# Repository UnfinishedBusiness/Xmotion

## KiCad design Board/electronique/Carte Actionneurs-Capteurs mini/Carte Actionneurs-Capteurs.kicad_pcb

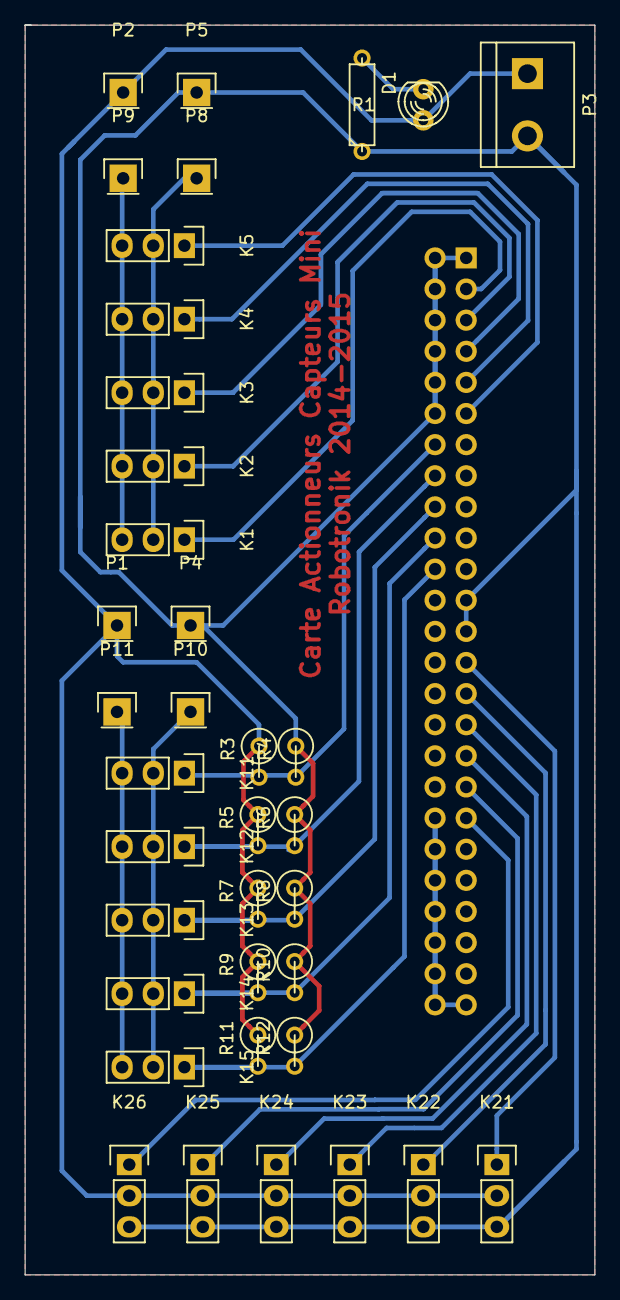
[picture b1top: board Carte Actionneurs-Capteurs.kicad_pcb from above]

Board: 2 copper layers, 46.5 x 102.0 mm, 38 parts (1 on the bottom side), 23 nets.

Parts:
D1: LED; LED-3MM
K1, K2, K3, K4, K5, K11, K12, K13, K14, K15, K21, K22, K23, K24, K25, K26: CONN_01X03; Pin_Header_Straight_1x03
P1, P2, P4, P5, P8, P9, P10, P11: CONN_1; Pin_Header_Straight_1x01
P3: CONN_2; bornier2
P6: CONN_25X2; Pin_Header_Straight_2x25
R1: R; R3
R3, R4, R5, R6, R7, R8, R9, R10, R11, R12: R; R1

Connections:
ADC1: K1.1, P6.3
ADC2: K2.1, P6.5
ADC3: K3.1, P6.7
ADC4: K4.1, P6.9
ADC5: K5.1, P6.11
IO1: K11.1, P6.14, R3.2, R4.2
IO2: K12.1, P6.16, R5.2, R6.2
IO3: K13.1, P6.18, R7.2, R8.2
IO4: K14.1, P6.20, R9.2, R10.2
IO5: K15.1, P6.22, R11.2, R12.2
unnamed: D1.2, R1.2
PWM1: K21.1, P6.27
PWM2: K22.1, P6.29
PWM3: K23.1, P6.31
PWM4: K24.1, P6.33
PWM5: K25.1, P6.35
PWM6: K26.1, P6.37
PWR_ADC_1: K1.2, K2.2, K3.2, K4.2, K5.2, P8.1
PWR_ADC_2: K1.3, K2.3, K3.3, K4.3, K5.3, P9.1
PWR_ADC_3: D1.1, K21.2, K22.2, K23.2, K24.2, K25.2, K26.2, P1.1, P2.1, P3.1, R3.1, R5.1, R7.1, R9.1, R11.1
PWR_ADC_4: K21.3, K22.3, K23.3, K24.3, K25.3, K26.3, P3.2, P4.1, P5.1, P6.1, P6.2, P6.4, P6.6, P6.8, P6.10, P6.12, P6.23, P6.25, P6.38, P6.40, P6.42, P6.44, P6.46, P6.48, P6.49, P6.50, R1.1, R4.1, R6.1, R8.1, R10.1, R12.1
PWR_IO_1: K11.2, K12.2, K13.2, K14.2, K15.2, P10.1
PWR_IO_2: K11.3, K12.3, K13.3, K14.3, K15.3, P11.1

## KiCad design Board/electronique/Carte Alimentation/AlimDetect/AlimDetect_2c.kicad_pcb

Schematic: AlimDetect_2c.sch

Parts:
C1: 0.33µ; C_0603_HandSoldering
C3: 0.1µ; C_0603_HandSoldering
C4: C; C_Radial_D18_L36_P7.5
D1, D6: LED; LED-3MM
D2: 1N5404; Diode_DO-201AD_Horizontal_RM15
D3, D4: LED; LED_0603
D5: ZENER; D3
F1: FUSE; Fuseholder5x20_horiz_open_inline_Type-I
K1: CONN_01X03; Pin_Header_Angled_1x03
P1, P2, P3: CONN_01X02; bornier2
P4: CONN_01X02; Pin_Header_Straight_1x02
R1, R2, R3, R5, R6, R7, R8, R9: R; R_0603_HandSoldering
R4: 820; Resistor_Horizontal_RM10mm
R10, R11: 15k; R_0603_HandSoldering
R12, R13: 150; R_0603_HandSoldering
R14: 82; R_0603_HandSoldering
R15: 380; Resistor_Horizontal_RM10mm
R16, R17: 250; R_0603_HandSoldering
U1: TLC274; SOIC-14_3.9x8.7mm_Pitch1.27mm
U3: 74LS08; SOIC-14_3.9x8.7mm_Pitch1.27mm
U4: KMIG1240; kmig1240
U5: 7805; TO-220_Neutral123_Horizontal

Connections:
+5V: C3.1, P2.2, R14.1, U3.14, U4.1, U5.3 (VO)
/Vref: D5.1, R14.2, U1.9, U1.13
/elec_redressé: C1.1, C4.1, D2.1, P3.2, U1.4, U5.1 (VI)
GND: C1.2, C3.2, C4.2, D1.1, D3.1, D4.1, D5.2, D6.2, K1.1, P1.1, P2.1, P3.1, R3.2, R6.1, R8.2, R10.2, R11.2, U1.11, U3.1, U3.2, U3.4, U3.5, U3.7, U3.9, U3.10, U5.2 (GND)
unnamed: D1.2, R4.2
unnamed: D2.2, F1.2, R4.1
unnamed: D3.2, R12.2
unnamed: D4.2, R13.2
unnamed: D6.1, R15.2
unnamed: F1.1, P1.2
unnamed: K1.2, R1.1, R7.1
unnamed: K1.3, R2.1, R15.1
unnamed: P4.1, U4.2
unnamed: P4.2, U3.11
unnamed: R1.2, R5.1, U1.2
unnamed: R2.2, R3.1, U1.3
unnamed: R6.2, R9.1, U1.6
unnamed: R7.2, R8.1, U1.5
unnamed: R10.1, R12.1, U1.14, U3.12
unnamed: R11.1, R13.1, U1.8, U3.13
unnamed: R5.2, R16.1, U1.1
unnamed: R16.2, U1.10
unnamed: R9.2, R17.1, U1.7
unnamed: R17.2, U1.12

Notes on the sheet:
IN_DETECT
IN_ELEC
ELEC_REGUL_5V

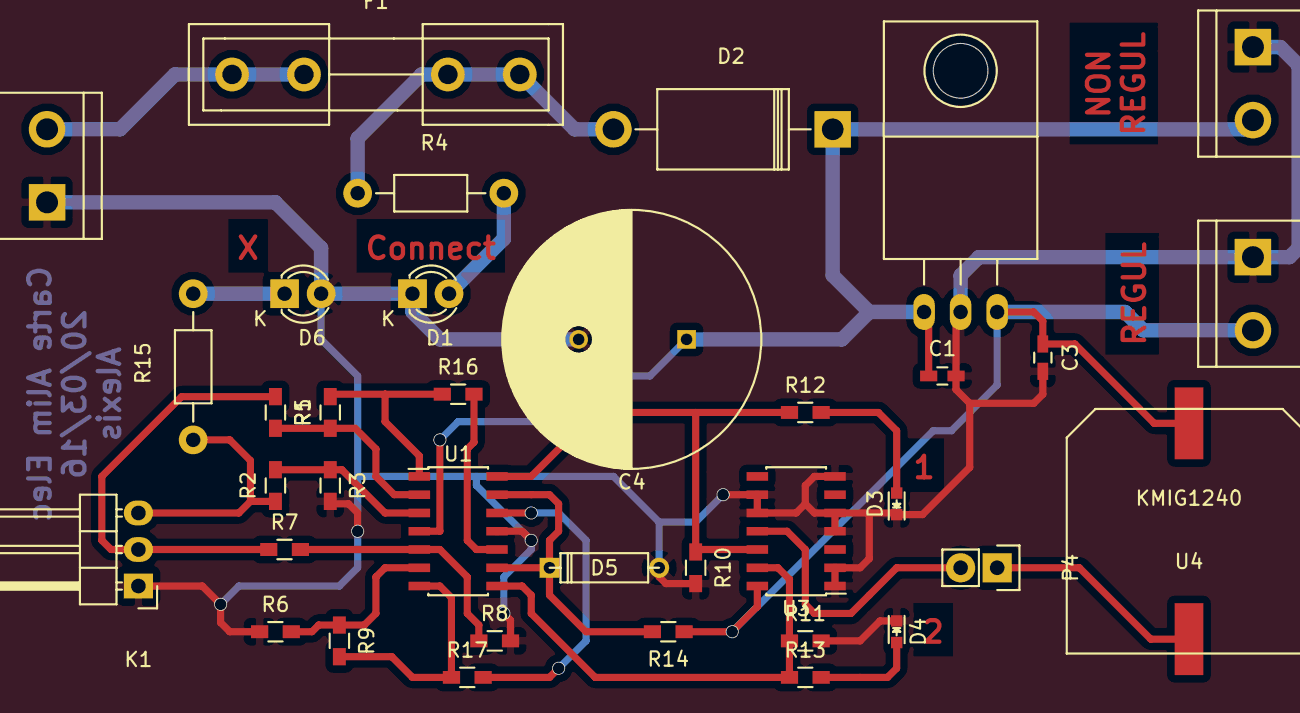
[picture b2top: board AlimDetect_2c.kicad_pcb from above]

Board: 2 copper layers, 36 parts (0 on the bottom side), 24 nets.

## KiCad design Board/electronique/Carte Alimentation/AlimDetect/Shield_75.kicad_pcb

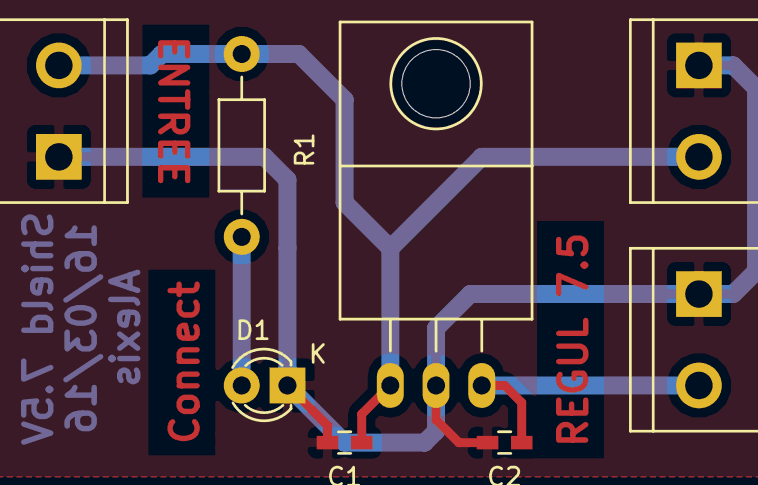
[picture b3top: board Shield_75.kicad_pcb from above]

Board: 2 copper layers, 8 parts (0 on the bottom side), 4 nets.

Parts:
C1, C2: C; C_0603_HandSoldering
D1: LED; LED-3MM
P1, P2, P3: CONN_01X02; bornier2
R1: R; Resistor_Horizontal_RM10mm
U1: 78S75C_correctPin; TO-220_Neutral123_Horizontal

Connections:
GND: C1.2, C2.2, D1.1, P1.1, P2.1, P3.1, U1.2
unnamed: C1.1, P1.2, P3.2, R1.1, U1.1
unnamed: C2.1, P2.2, U1.3
unnamed: D1.2, R1.2

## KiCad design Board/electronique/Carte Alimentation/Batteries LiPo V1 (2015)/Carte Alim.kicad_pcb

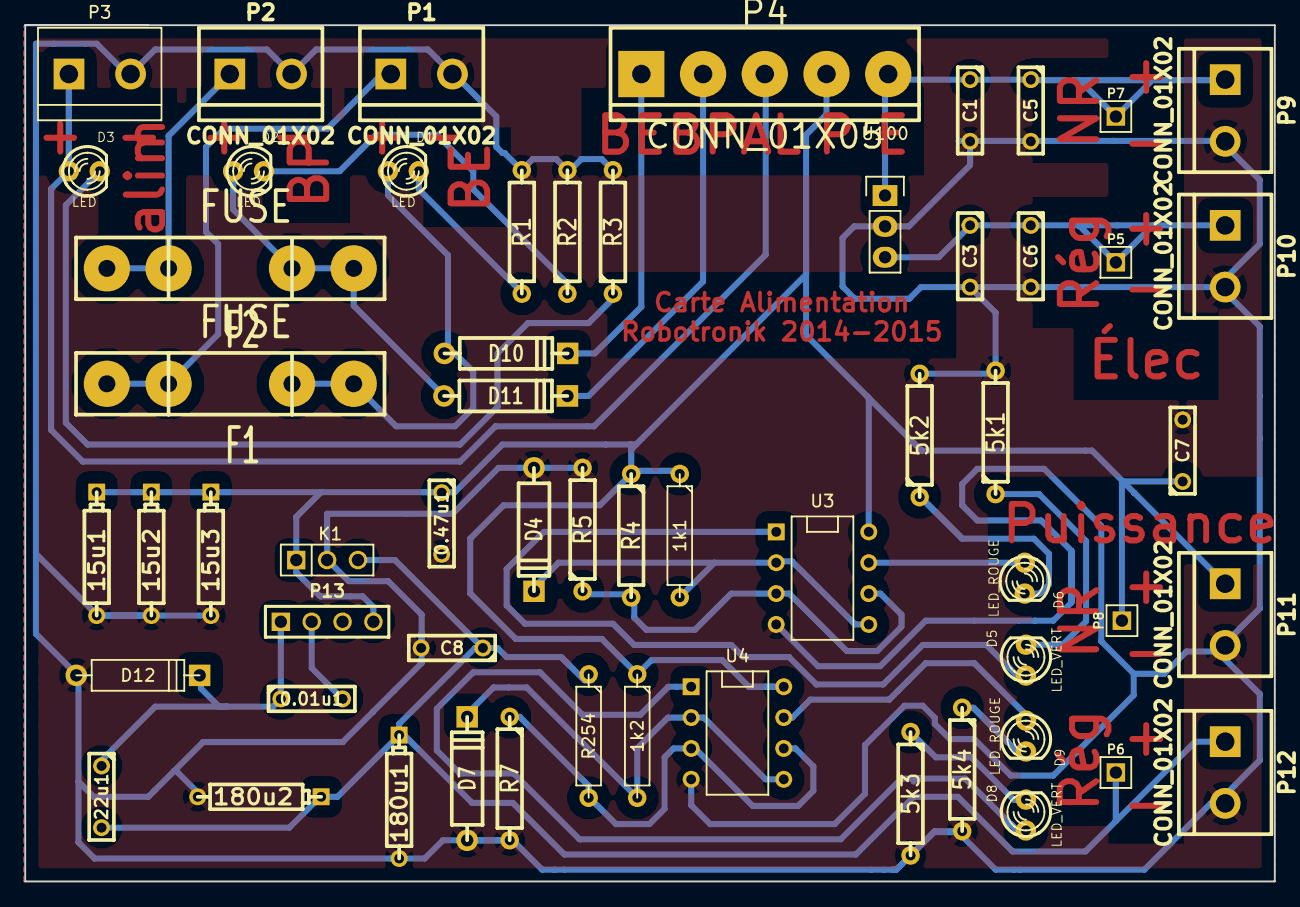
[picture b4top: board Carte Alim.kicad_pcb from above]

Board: 2 copper layers, 102.9 x 70.5 mm, 58 parts (0 on the bottom side), 29 nets.

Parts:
0.01u1, 0.47u1: C; C2
1k1, 1k2, 5k1, 5k2, 5k3, 5k4: R; R4
15u1, 15u2, 15u3, 180u1, 180u2: CP1; CP4
22u1: INDUCTOR; C2
C1, C3, C5, C6, C7, C8: C; C2
D1, D2, D3: LED; LED-3MM
D4, D7: ZENER; D4
D5, D8: LED_VERT; LED-3MM
D6, D9: LED_ROUGE; LED-3MM
D10, D11: DIODE; D4
D12: DIODESCH; D4
F1, F2: FUSE; FUSE5-20
K1: CONN_01X03; PIN_ARRAY_3X1
P1, P2, P3, P9, P10, P11, P12: CONN_01X02; bornier2
P4: CONN_01X05; bornier5
P5, P6, P7, P8: CONN_01X01; PIN_ARRAY_1
P13: CONN_01X04; PIN_ARRAY_4x1
R1, R2, R3, R4, R5, R7, R254: R; R4
U3, U4: LM2903; DIP-8__300
U100: 7805; Pin_Header_Straight_1x03

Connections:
/alim_elec: C3.1, C6.1, P5.1, P10.1, U100.3
/alim_elec_non_regul: C1.1, C5.1, P4.5, P7.1, P9.1, U100.1
/alim_puissance_non_regul: 0.47u1.1, 1k1.1, 1k2.1, 15u1.1, 15u2.1, 15u3.1, C7.1, K1.1, P4.4, P8.1, P11.1, P13.4, R4.1, U3.8, U4.8
/alim_puissance_regul: 22u1.2, 180u1.1, 180u2.1, C8.1, K1.3, P6.1, P12.1, R254.1
GND: 0.47u1.2, 5k1.2, 5k2.2, 5k3.2, 5k4.2, 15u1.2, 15u2.2, 15u3.2, 180u1.2, 180u2.2, C1.2, C3.2, C5.2, C6.2, C7.2, C8.2, D4.1, D7.1, D12.1, K1.2, P1.2, P2.2, P3.2, P9.2, P10.2, P11.2, P12.2, R1.2, R2.2, R3.2, R5.2, R7.2, U3.4, U4.4, U100.2
unnamed: 0.01u1.1, 22u1.1, D12.2, P13.1
unnamed: 0.01u1.2, P13.2
unnamed: 1k1.2, D4.2, U3.2, U3.5
unnamed: 1k2.2, D7.2, U4.2, U4.5
unnamed: 5k1.1, D5.2
unnamed: 5k2.1, D6.2
unnamed: 5k3.1, D8.2
unnamed: 5k4.1, D9.2
unnamed: D1.1, D10.1, F1.2
unnamed: D1.2, R1.1
unnamed: D2.2, R2.1
unnamed: D3.1, P3.1, P4.3
unnamed: D3.2, R3.1
unnamed: D5.1, U3.1
unnamed: D6.1, U3.7
unnamed: D8.1, U4.1
unnamed: D9.1, U4.7
unnamed: D10.2, P4.1
unnamed: D2.1, D11.1, F2.2
unnamed: D11.2, P4.2
unnamed: F1.1, P1.1
unnamed: F2.1, P2.1
unnamed: R4.2, R5.1, U3.3, U3.6
unnamed: R7.1, R254.2, U4.3, U4.6

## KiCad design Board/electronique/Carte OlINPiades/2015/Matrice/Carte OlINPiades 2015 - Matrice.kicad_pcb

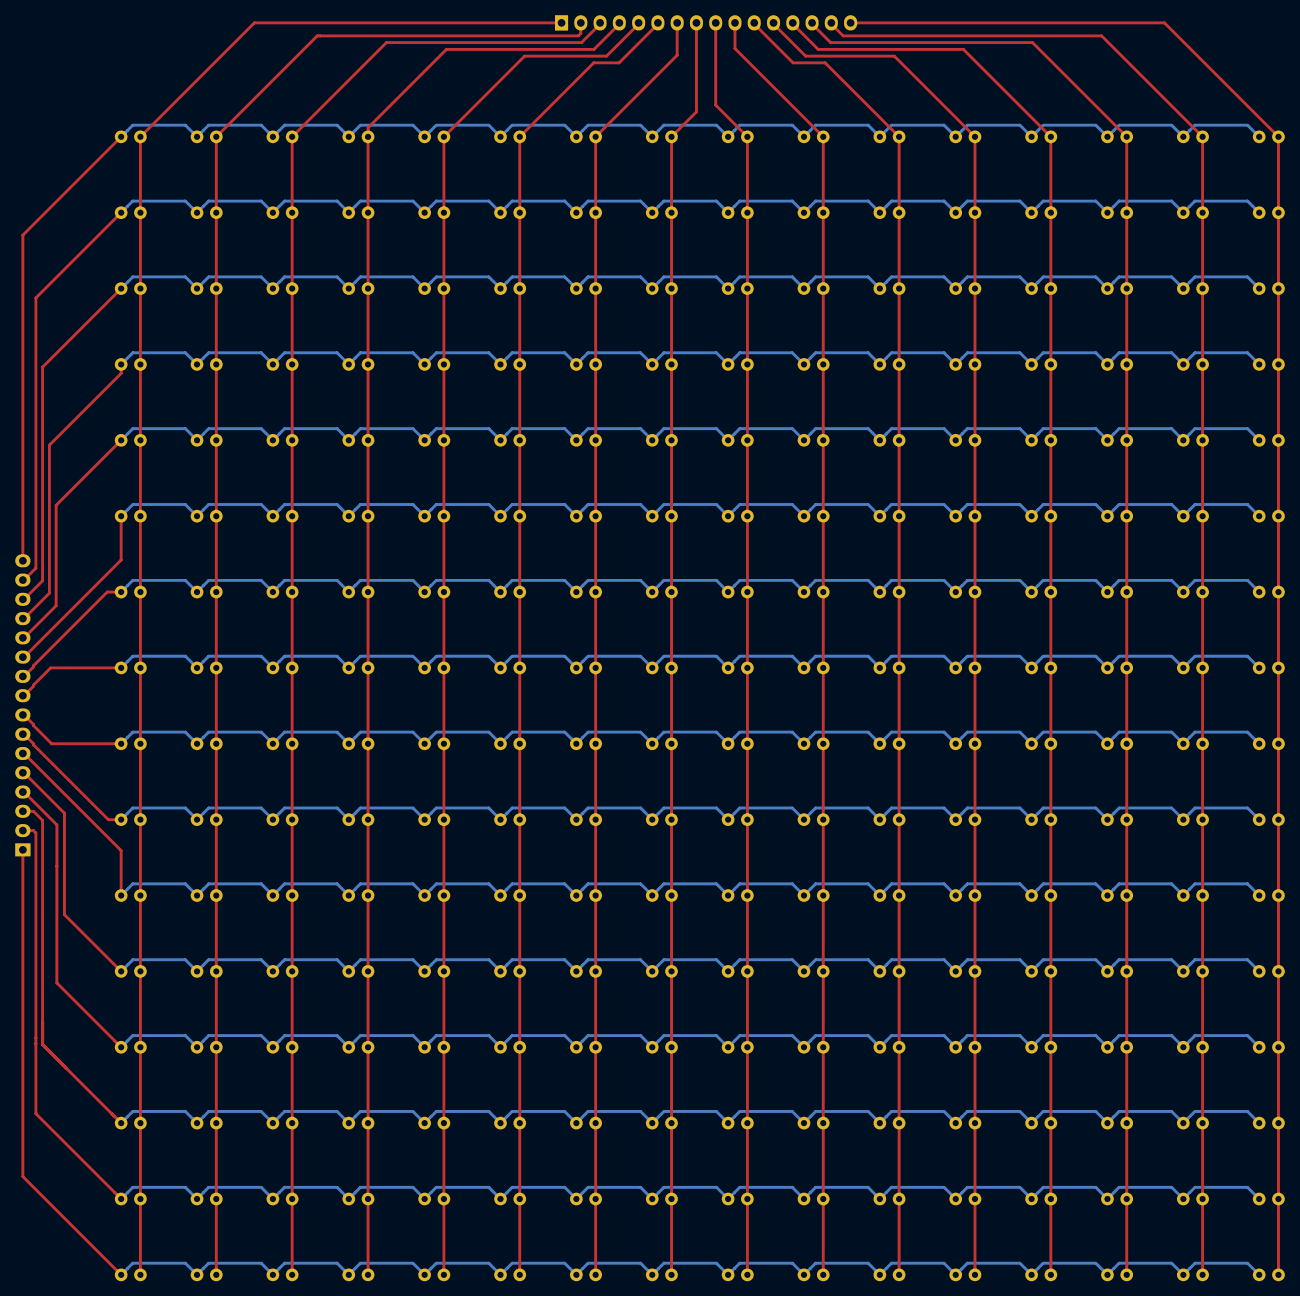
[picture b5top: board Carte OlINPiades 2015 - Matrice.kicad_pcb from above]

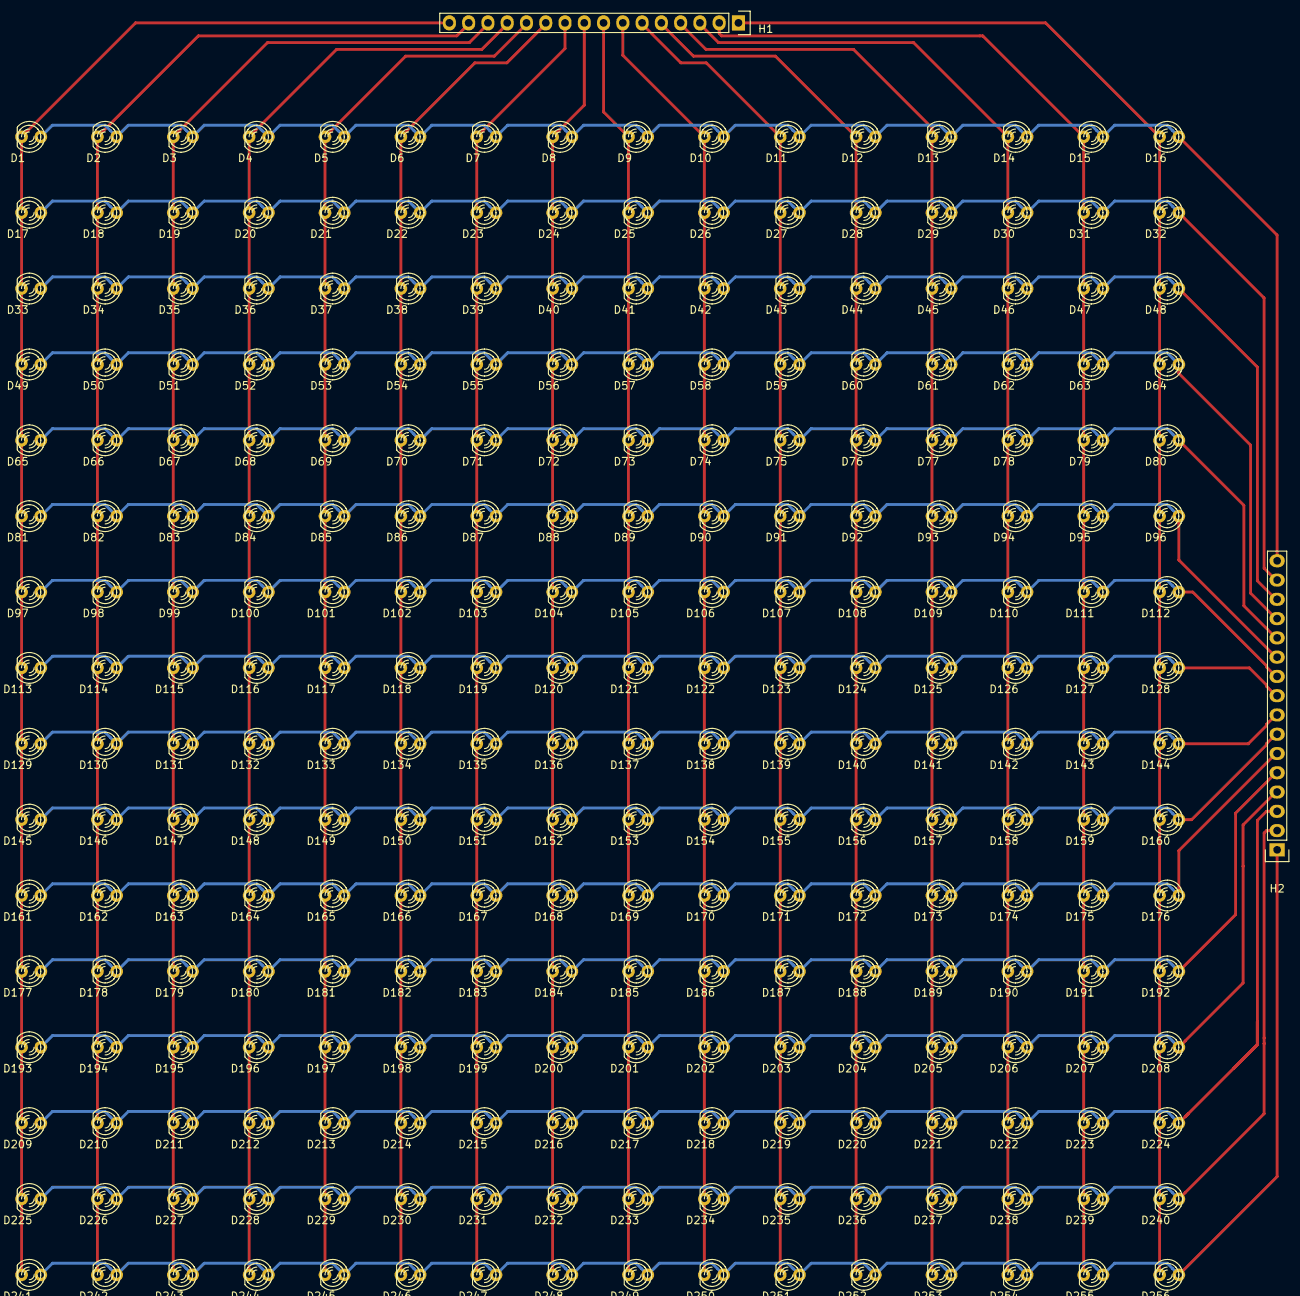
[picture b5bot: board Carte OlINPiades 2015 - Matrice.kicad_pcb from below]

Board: 2 copper layers, 258 parts (258 on the bottom side), 32 nets.

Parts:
D1, D2, D3, D4, D5, D6, D7, D8, D9, D10, D11, D12, D13, D14, D15, D16, D17, D18, D19, D20, D21, D22, D23, D24, D25, D26, D27, D28, D29, D30, D31, D32, D33, D34, D35, D36, D37, D38, D39, D40, D41, D42, D43, D44, D45, D46, D47, D48, D49, D50, D51, D52, D53, D54, D55, D56, D57, D58, D59, D60, D61, D62, D63, D64, D65, D66, D67, D68, D69, D70, D71, D72, D73, D74, D75, D76, D77, D78, D79, D80, D81, D82, D83, D84, D85, D86, D87, D88, D89, D90, D91, D92, D93, D94, D95, D96, D97, D98, D99, D100, D101, D102, D103, D104, D105, D106, D107, D108, D109, D110, D111, D112, D113, D114, D115, D116, D117, D118, D119, D120, D121, D122, D123, D124, D125, D126, D127, D128, D129, D130, D131, D132, D133, D134, D135, D136, D137, D138, D139, D140, D141, D142, D143, D144, D145, D146, D147, D148, D149, D150, D151, D152, D153, D154, D155, D156, D157, D158, D159, D160, D161, D162, D163, D164, D165, D166, D167, D168, D169, D170, D171, D172, D173, D174, D175, D176, D177, D178, D179, D180, D181, D182, D183, D184, D185, D186, D187, D188, D189, D190, D191, D192, D193, D194, D195, D196, D197, D198, D199, D200, D201, D202, D203, D204, D205, D206, D207, D208, D209, D210, D211, D212, D213, D214, D215, D216, D217, D218, D219, D220, D221, D222, D223, D224, D225, D226, D227, D228, D229, D230, D231, D232, D233, D234, D235, D236, D237, D238, D239, D240, D241, D242, D243, D244, D245, D246, D247, D248, D249, D250, D251, D252, D253, D254, D255, D256: LED; LED-3MM
H1, H2: PinHeader; Pin_Header_Straight_1x16

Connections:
unnamed: D1.1, D2.1, D3.1, D4.1, D5.1, D6.1, D7.1, D8.1, D9.1, D10.1, D11.1, D12.1, D13.1, D14.1, D15.1, D16.1, H2.16
unnamed: D1.2, D17.2, D33.2, D49.2, D65.2, D81.2, D97.2, D113.2, D129.2, D145.2, D161.2, D177.2, D193.2, D209.2, D225.2, D241.2, H1.16
unnamed: D10.2, D26.2, D42.2, D58.2, D74.2, D90.2, D106.2, D122.2, D138.2, D154.2, D170.2, D186.2, D202.2, D218.2, D234.2, D250.2, H1.7
unnamed: D17.1, D18.1, D19.1, D20.1, D21.1, D22.1, D23.1, D24.1, D25.1, D26.1, D27.1, D28.1, D29.1, D30.1, D31.1, D32.1, H2.15
unnamed: D33.1, D34.1, D35.1, D36.1, D37.1, D38.1, D39.1, D40.1, D41.1, D42.1, D43.1, D44.1, D45.1, D46.1, D47.1, D48.1, H2.14
unnamed: D49.1, D50.1, D51.1, D52.1, D53.1, D54.1, D55.1, D56.1, D57.1, D58.1, D59.1, D60.1, D61.1, D62.1, D63.1, D64.1, H2.13
unnamed: D65.1, D66.1, D67.1, D68.1, D69.1, D70.1, D71.1, D72.1, D73.1, D74.1, D75.1, D76.1, D77.1, D78.1, D79.1, D80.1, H2.12
unnamed: D81.1, D82.1, D83.1, D84.1, D85.1, D86.1, D87.1, D88.1, D89.1, D90.1, D91.1, D92.1, D93.1, D94.1, D95.1, D96.1, H2.11
unnamed: D97.1, D98.1, D99.1, D100.1, D101.1, D102.1, D103.1, D104.1, D105.1, D106.1, D107.1, D108.1, D109.1, D110.1, D111.1, D112.1, H2.10
unnamed: D4.2, D20.2, D36.2, D52.2, D68.2, D84.2, D100.2, D116.2, D132.2, D148.2, D164.2, D180.2, D196.2, D212.2, D228.2, D244.2, H1.13
unnamed: D5.2, D21.2, D37.2, D53.2, D69.2, D85.2, D101.2, D117.2, D133.2, D149.2, D165.2, D181.2, D197.2, D213.2, D229.2, D245.2, H1.12
unnamed: D6.2, D22.2, D38.2, D54.2, D70.2, D86.2, D102.2, D118.2, D134.2, D150.2, D166.2, D182.2, D198.2, D214.2, D230.2, D246.2, H1.11
unnamed: D7.2, D23.2, D39.2, D55.2, D71.2, D87.2, D103.2, D119.2, D135.2, D151.2, D167.2, D183.2, D199.2, D215.2, D231.2, D247.2, H1.10
unnamed: D8.2, D24.2, D40.2, D56.2, D72.2, D88.2, D104.2, D120.2, D136.2, D152.2, D168.2, D184.2, D200.2, D216.2, D232.2, D248.2, H1.9
unnamed: D9.2, D25.2, D41.2, D57.2, D73.2, D89.2, D105.2, D121.2, D137.2, D153.2, D169.2, D185.2, D201.2, D217.2, D233.2, D249.2, H1.8
unnamed: D11.2, D27.2, D43.2, D59.2, D75.2, D91.2, D107.2, D123.2, D139.2, D155.2, D171.2, D187.2, D203.2, D219.2, D235.2, D251.2, H1.6
unnamed: D12.2, D28.2, D44.2, D60.2, D76.2, D92.2, D108.2, D124.2, D140.2, D156.2, D172.2, D188.2, D204.2, D220.2, D236.2, D252.2, H1.5
unnamed: D13.2, D29.2, D45.2, D61.2, D77.2, D93.2, D109.2, D125.2, D141.2, D157.2, D173.2, D189.2, D205.2, D221.2, D237.2, D253.2, H1.4
unnamed: D14.2, D30.2, D46.2, D62.2, D78.2, D94.2, D110.2, D126.2, D142.2, D158.2, D174.2, D190.2, D206.2, D222.2, D238.2, D254.2, H1.3
unnamed: D15.2, D31.2, D47.2, D63.2, D79.2, D95.2, D111.2, D127.2, D143.2, D159.2, D175.2, D191.2, D207.2, D223.2, D239.2, D255.2, H1.2
unnamed: D16.2, D32.2, D48.2, D64.2, D80.2, D96.2, D112.2, D128.2, D144.2, D160.2, D176.2, D192.2, D208.2, D224.2, D240.2, D256.2, H1.1
unnamed: D113.1, D114.1, D115.1, D116.1, D117.1, D118.1, D119.1, D120.1, D121.1, D122.1, D123.1, D124.1, D125.1, D126.1, D127.1, D128.1, H2.9
unnamed: D2.2, D18.2, D34.2, D50.2, D66.2, D82.2, D98.2, D114.2, D130.2, D146.2, D162.2, D178.2, D194.2, D210.2, D226.2, D242.2, H1.15
unnamed: D3.2, D19.2, D35.2, D51.2, D67.2, D83.2, D99.2, D115.2, D131.2, D147.2, D163.2, D179.2, D195.2, D211.2, D227.2, D243.2, H1.14
unnamed: D129.1, D130.1, D131.1, D132.1, D133.1, D134.1, D135.1, D136.1, D137.1, D138.1, D139.1, D140.1, D141.1, D142.1, D143.1, D144.1, H2.8
unnamed: D145.1, D146.1, D147.1, D148.1, D149.1, D150.1, D151.1, D152.1, D153.1, D154.1, D155.1, D156.1, D157.1, D158.1, D159.1, D160.1, H2.7
unnamed: D161.1, D162.1, D163.1, D164.1, D165.1, D166.1, D167.1, D168.1, D169.1, D170.1, D171.1, D172.1, D173.1, D174.1, D175.1, D176.1, H2.6
unnamed: D177.1, D178.1, D179.1, D180.1, D181.1, D182.1, D183.1, D184.1, D185.1, D186.1, D187.1, D188.1, D189.1, D190.1, D191.1, D192.1, H2.5
unnamed: D193.1, D194.1, D195.1, D196.1, D197.1, D198.1, D199.1, D200.1, D201.1, D202.1, D203.1, D204.1, D205.1, D206.1, D207.1, D208.1, H2.4
unnamed: D209.1, D210.1, D211.1, D212.1, D213.1, D214.1, D215.1, D216.1, D217.1, D218.1, D219.1, D220.1, D221.1, D222.1, D223.1, D224.1, H2.3
unnamed: D225.1, D226.1, D227.1, D228.1, D229.1, D230.1, D231.1, D232.1, D233.1, D234.1, D235.1, D236.1, D237.1, D238.1, D239.1, D240.1, H2.2
unnamed: D241.1, D242.1, D243.1, D244.1, D245.1, D246.1, D247.1, D248.1, D249.1, D250.1, D251.1, D252.1, D253.1, D254.1, D255.1, D256.1, H2.1

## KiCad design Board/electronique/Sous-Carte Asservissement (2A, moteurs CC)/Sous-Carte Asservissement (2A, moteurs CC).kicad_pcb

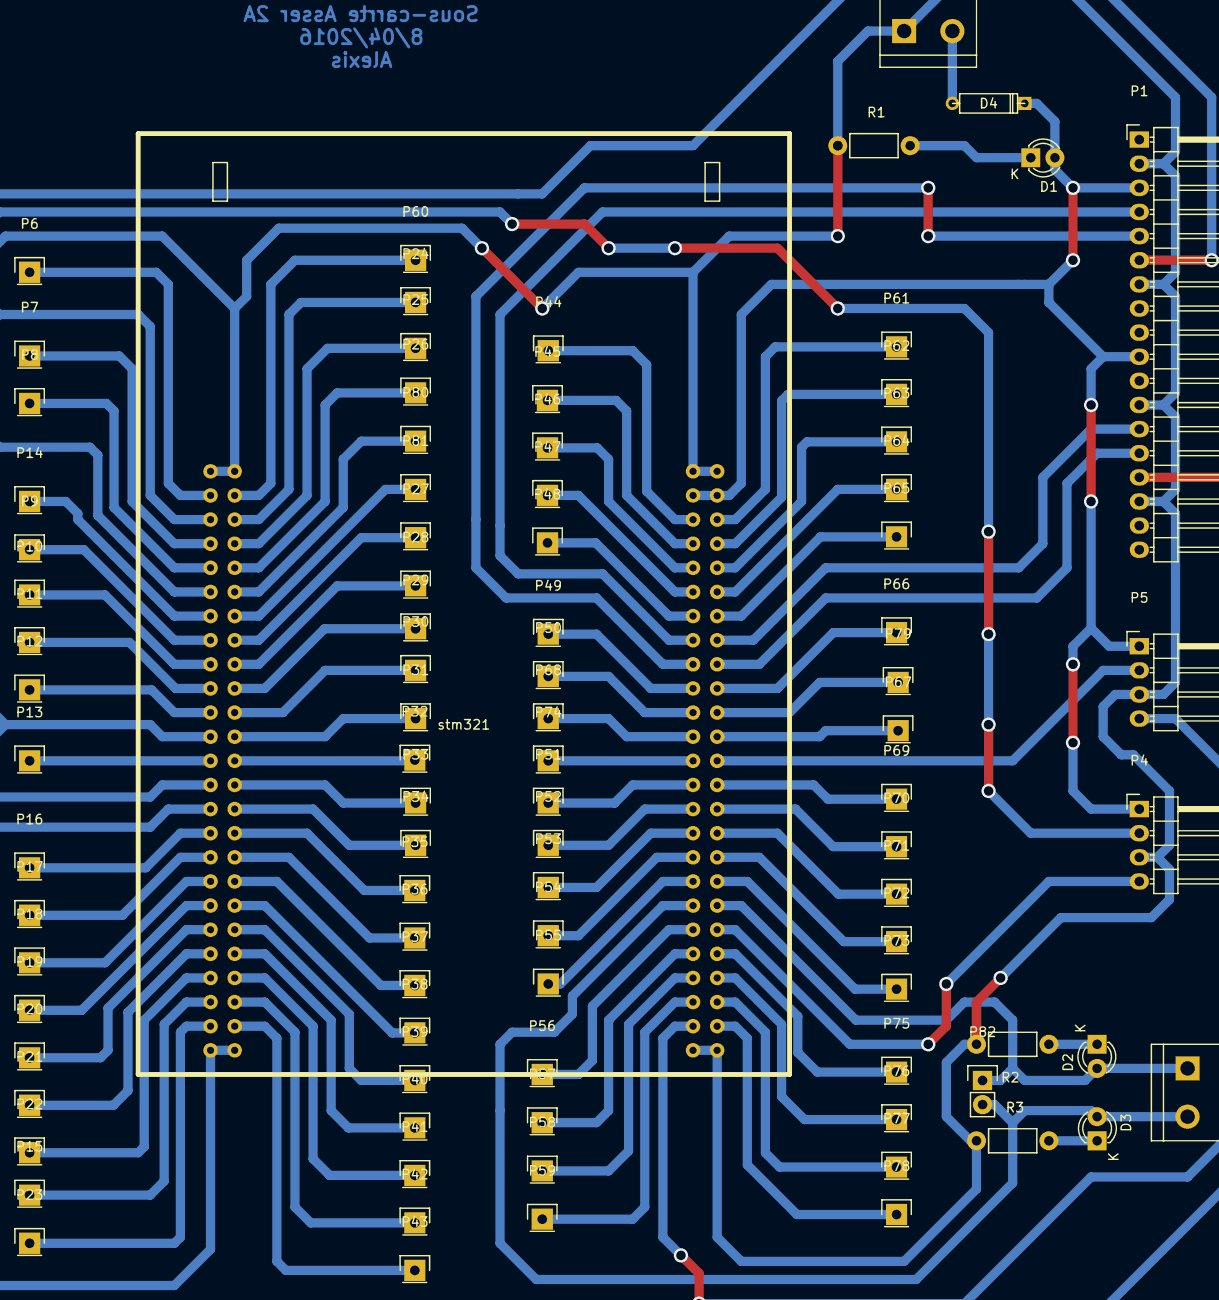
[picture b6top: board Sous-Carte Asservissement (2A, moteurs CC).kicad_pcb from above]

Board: 2 copper layers, 90 parts (0 on the bottom side), 94 nets.

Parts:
D1, D2, D3: LED; LED-3MM
D4: D; D3
P1: CONN_01X18; Pin_Header_Angled_1x18
P2, P3: CONN_01X02; bornier2
P4, P5: CONN_01X04; Pin_Header_Angled_1x04
P6, P7, P8, P9, P10, P11, P12, P13, P14, P15, P16, P17, P18, P19, P20, P21, P22, P23, P24, P25, P26, P27, P28, P29, P30, P31, P32, P33, P34, P35, P36, P37, P38, P39, P40, P41, P42, P43, P44, P45, P46, P47, P48, P49, P50, P51, P52, P53, P54, P55, P56, P57, P58, P59, P60, P61, P62, P63, P64, P65, P66, P67, P68, P69, P70, P71, P72, P73, P74, P75, P76, P77, P78, P79, P80, P81: CONN_01X01; Pin_Header_Straight_1x01
P82: CONN_01X02; Pin_Header_Straight_1x02
R1, R2, R3: 150; Resistor_Horizontal_RM7mm
stm321: STM32F407-Discovery; STM32F407

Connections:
+5V: D1.2, D4.1, P1.3, P1.10, P4.1, P5.1, stm321.53, stm321.54
GND: P1.2, P1.7, P1.12, P1.16, P2.1, P4.3, P5.3, R1.1, R2.2, R3.1, stm321.1, stm321.2, stm321.5, stm321.23, stm321.49, stm321.50, stm321.51, stm321.52, stm321.99, stm321.100
M1I1: P1.5, stm321.67
M1I2: P1.4, stm321.65
M1PWM: P1.6, stm321.27
M2PWM: P1.15, stm321.29
M2_I1: P1.14, stm321.68
M2_I2: P1.13, stm321.66
unnamed: D1.1, R1.2
unnamed: D2.1, R2.1
unnamed: D3.1, R3.2
unnamed: D4.2, P2.2
unnamed: P6.1, stm321.3
unnamed: P7.1, stm321.7
unnamed: P8.1, stm321.9
unnamed: P9.1, stm321.15
unnamed: P10.1, stm321.17
unnamed: P11.1, stm321.19
unnamed: P12.1, stm321.21
unnamed: P13.1, stm321.25
unnamed: P14.1, stm321.13
unnamed: P15.1, stm321.45
unnamed: P16.1, stm321.31
unnamed: P17.1, stm321.33
unnamed: P18.1, stm321.35
unnamed: P19.1, stm321.37
unnamed: P20.1, stm321.39
unnamed: P21.1, stm321.41
unnamed: P22.1, stm321.43
unnamed: P23.1, stm321.47
unnamed: P24.1, stm321.6
unnamed: P25.1, stm321.8
unnamed: P26.1, stm321.10
unnamed: P27.1, stm321.16
unnamed: P28.1, stm321.18
unnamed: P29.1, stm321.20
unnamed: P30.1, stm321.22
unnamed: P31.1, stm321.24
unnamed: P32.1, stm321.26
unnamed: P33.1, stm321.28
unnamed: P34.1, stm321.30
unnamed: P35.1, stm321.32
unnamed: P36.1, stm321.34
unnamed: P37.1, stm321.36
unnamed: P38.1, stm321.38
unnamed: P39.1, stm321.40
unnamed: P40.1, stm321.42
unnamed: P41.1, stm321.44
unnamed: P42.1, stm321.46
unnamed: P43.1, stm321.48
unnamed: P44.1, stm321.55
unnamed: P45.1, stm321.57
unnamed: P46.1, stm321.59
unnamed: P47.1, stm321.61
unnamed: P48.1, stm321.63
unnamed: P49.1, stm321.69
unnamed: P50.1, stm321.71
unnamed: P51.1, stm321.77
unnamed: P52.1, stm321.79
unnamed: P53.1, stm321.81
unnamed: P54.1, stm321.83
unnamed: P55.1, stm321.85
unnamed: P56.1, stm321.89
unnamed: P57.1, stm321.91
unnamed: P58.1, stm321.93
unnamed: P59.1, stm321.95
unnamed: P60.1, stm321.4
unnamed: P61.1, stm321.56
unnamed: P62.1, stm321.58
unnamed: P63.1, stm321.60
unnamed: P64.1, stm321.62
unnamed: P65.1, stm321.64
unnamed: P66.1, stm321.70
unnamed: P67.1, stm321.74
unnamed: P68.1, stm321.73
unnamed: P69.1, stm321.78
unnamed: P70.1, stm321.80
unnamed: P71.1, stm321.82
unnamed: P72.1, stm321.84
unnamed: P73.1, stm321.86
unnamed: P74.1, stm321.75
unnamed: P75.1, stm321.92
unnamed: P76.1, stm321.94
unnamed: P77.1, stm321.96
unnamed: P78.1, stm321.98
unnamed: P79.1, stm321.72
unnamed: P80.1, stm321.12
unnamed: P81.1, stm321.14
TIM2_CH1: P4.4, stm321.90
TIM2_CH2: P4.2, stm321.11
TIM3_CH1: P5.4, stm321.97
TIM3_CH2: P5.2, stm321.76
UART_RX: D2.2, P3.1, P82.1, stm321.88
UART_TX: D3.2, P3.2, P82.2, stm321.87

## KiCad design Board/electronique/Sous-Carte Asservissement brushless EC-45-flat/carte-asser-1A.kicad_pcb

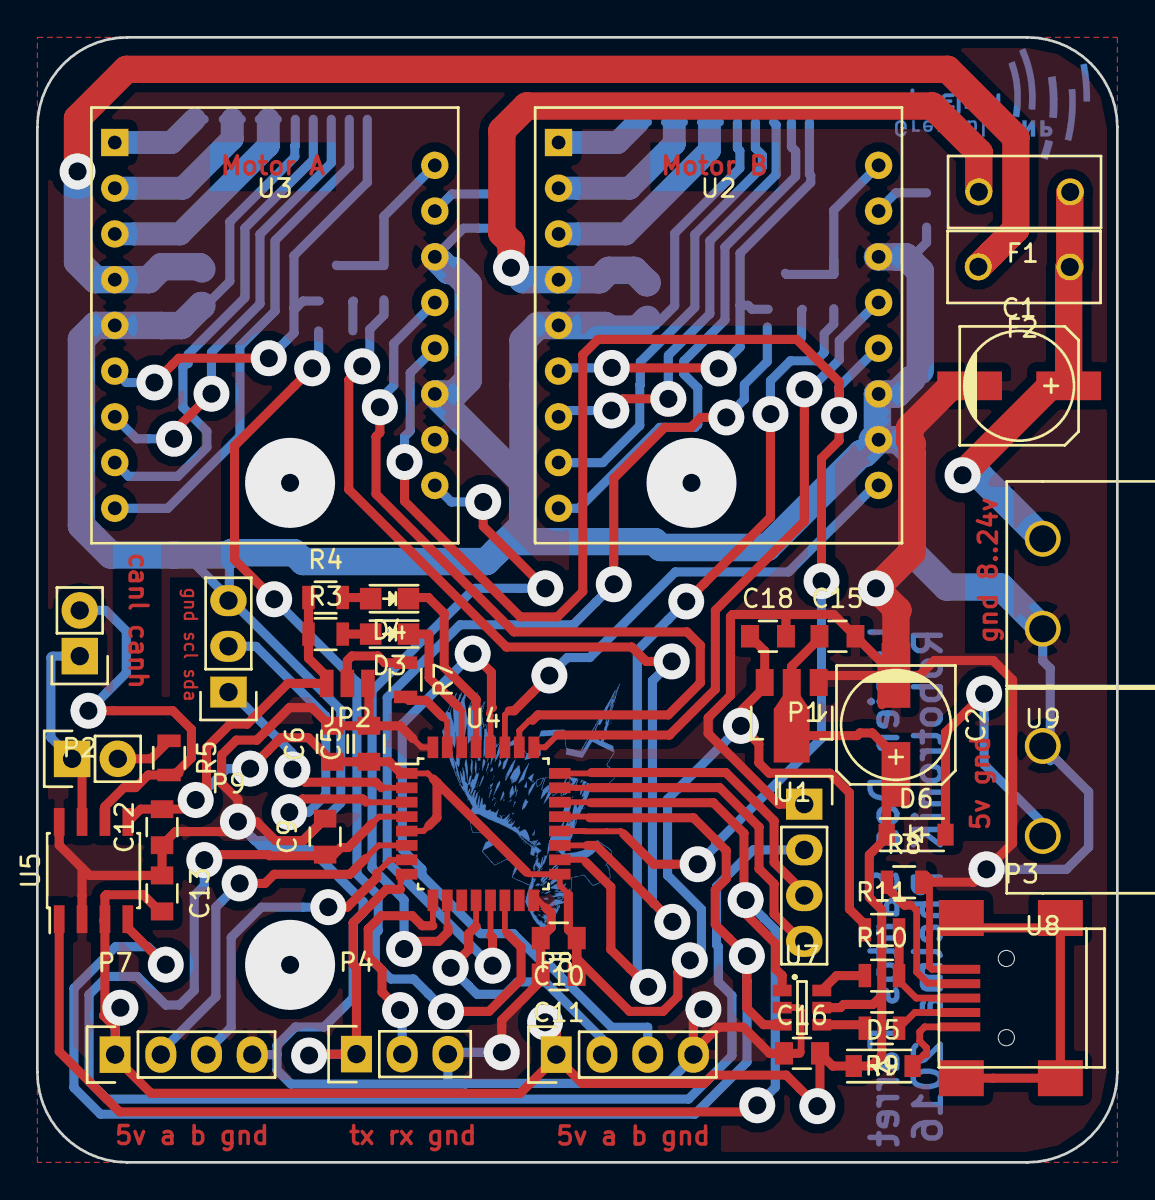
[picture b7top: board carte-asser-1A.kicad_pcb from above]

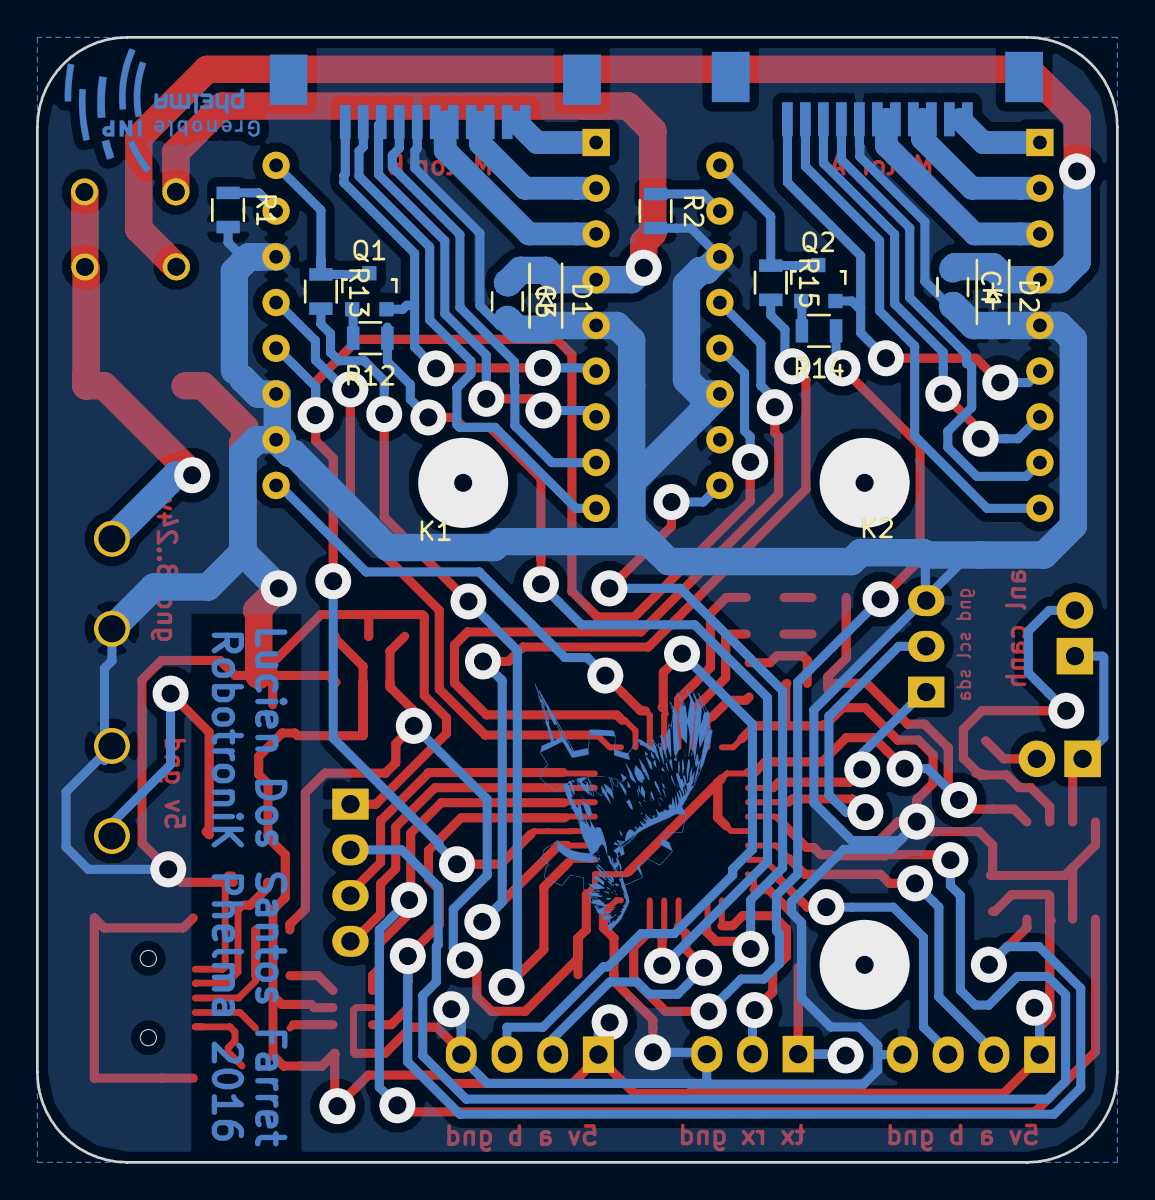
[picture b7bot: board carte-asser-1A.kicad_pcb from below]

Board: 2 copper layers, 60.0 x 62.5 mm, 57 parts (14 on the bottom side), 64 nets.

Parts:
C1: 100u/35v EEEHA1V101XP; c_elec_6.3x7.7
C2: 100u; c_elec_6.3x5.8
C3, C4: 45nF/50v; C_0805
C5, C9, C12, C13, C16: 100n; C_0805
C6: 4.7u; C_0805
C10: 10n; C_0805
C11, C15, C18: 1u; C_0805
D1, D2: Schottky/26V MBR0530T1G; SOD-123
D3, D4: LED; LED_0805
D5, D6: MBR0530T1G; SOD-123
F1, F2: FUSE/3A MF-R300; Fuse_TE5_Littlefuse-395Series
JP1: CAN termination; Pin_Header_Straight_1x02
JP2: boot mode; jumper_switch_3
K1, K2: Maxon-200142; Molex-52207-0433
P1: swdio; Pin_Header_Straight_1x04
P2: CAN bus; Pin_Header_Straight_1x02
P3: usb; USB_Mini-B
P4: serial bus; Socket_Strip_Straight_1x03
P7: encoder 1; Socket_Strip_Straight_1x04
P8: encoder 2; Socket_Strip_Straight_1x04
P9: i2c bus; Pin_Header_Straight_1x03
Q1, Q2: BC807; SOT-23
R1, R2, R7, R12, R14: 10k; R_0805
R3: 1K; R_0805
R4, R13, R15: 1k; R_0805
R5: 120; R_0805
R8: 10K; R_0805
R9, R10: 22; R_0805
R11: 1.5k; R_0805
U1: MCP1702; SOT89-3_Housing
U2, U3: DEC24/2; DE24-2
U4: stm32f042k6tx; LQFP-32_7x7mm_Pitch0.8mm
U5: MCP2562; SOIC-8_3.9x4.9mm_Pitch1.27mm
U7: USBLC6-2; SOT-23-6
U8: 5v input; B-plug-5mm
U9: 12v input; B-plug-5mm

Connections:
+3V3: C5.1, C6.1, C10.1, C11.1, C12.2, C18.1, JP2.3, R3.1, R4.1, R11.1, U1.3, U4.1, U4.5, U4.17, U5.5
+5V: C2.1, C13.2, C15.1, C16.2, D5.1, D6.1, P7.1, P8.1, U1.2, U5.3, U7.5
+5V_weak1: K1.11, Q1.2, U2.6
+5V_weak2: K2.11, Q2.2, U3.6
+24V: C1.1, F1.1, F2.1, U9.2
/brushless-part/W1_1: K1.1, K1.2, U2.1
/brushless-part/W1_2: K1.3, K1.4, U2.2
/brushless-part/W1_3: K1.5, K1.6, U2.3
/brushless-part/W2_1: K2.1, K2.2, U3.1
/brushless-part/W2_2: K2.3, K2.4, U3.2
/brushless-part/W2_3: K2.5, K2.6, U3.3
/brushless-part/motor1_speed: Q1.3, R13.1, U2.17
/brushless-part/motor2_speed: Q2.3, R15.1, U3.17
/brushless-part/power1: C3.1, D1.1, F1.2, U2.4
/brushless-part/power2: C4.1, D2.1, F2.2, U3.4
/encoder-part/encoder1_1: P7.2, U4.6
/encoder-part/encoder1_2: P7.3, U4.7
/encoder-part/encoder2_1: P8.2, U4.12
/encoder-part/encoder2_2: P8.3, U4.28
/serial-part/rx: P4.1, U4.8
/serial-part/tx: P4.2, U4.9
/uC-part/can_rx: U4.21, U5.4, U7.3
/uC-part/can_tx: U4.22, U5.1, U7.1
/uC-part/gpio_direction1: U2.14, U4.25
/uC-part/gpio_direction2: U3.14, U4.26
/uC-part/gpio_enable: U2.13, U3.13, U4.20
/uC-part/gpio_ready1: U2.10, U4.27
/uC-part/gpio_ready2: U3.10, U4.10
/uC-part/i2c_scl: P9.2, U4.3
/uC-part/i2c_sda: P9.1, U4.2
/uC-part/led1: D4.1, U4.29
/uC-part/led2: D3.1, U4.30
/uC-part/nrst: C9.1, P1.2, U4.4
/uC-part/pwm1_neg: R12.1, U4.13
/uC-part/pwm1_pos: R13.2, U4.18
/uC-part/pwm2_neg: R14.1, U4.14
/uC-part/pwm2_pos: R15.2, U4.19
/uC-part/swclk: P1.3, U4.24
/uC-part/swdio: P1.4, U4.23
GND: C1.2, C2.2, C3.2, C4.2, C5.2, C6.2, C9.2, C10.2, C11.2, C12.1, C13.1, C15.2, C16.1, C18.2, D1.2, D2.2, JP2.1, K1.7, K2.7, P1.1, P3.5, P4.3, P7.4, P8.4, P9.3, R1.2, R2.2, R8.2, U1.1, U2.5, U2.11, U2.12, U2.15, U3.5, U3.11, U3.12, U3.15, U4.16, U4.32, U5.2, U5.8, U7.2, U8.2, U9.1
unnamed: D3.2, R3.2
unnamed: D4.2, R4.2
unnamed: D5.2, P3.1
unnamed: D6.2, U8.1
unnamed: JP1.1, P2.1, U5.7
unnamed: JP1.2, R5.1
unnamed: JP2.2, R7.1
unnamed: K1.8, U2.8
unnamed: K1.9, U2.7
unnamed: K1.10, U2.9
unnamed: K2.8, U3.8
unnamed: K2.9, U3.7
unnamed: K2.10, U3.9
unnamed: P2.2, R5.2, U5.6
unnamed: P3.2, R9.1
unnamed: P3.3, R10.2, R11.2
unnamed: P3.4, R8.1
unnamed: Q1.1, R12.2
unnamed: Q2.1, R14.2
unnamed: R1.1, U2.16
unnamed: R2.1, U3.16
unnamed: R7.2, U4.31
unnamed: R9.2, U7.4
unnamed: R10.1, U7.6
